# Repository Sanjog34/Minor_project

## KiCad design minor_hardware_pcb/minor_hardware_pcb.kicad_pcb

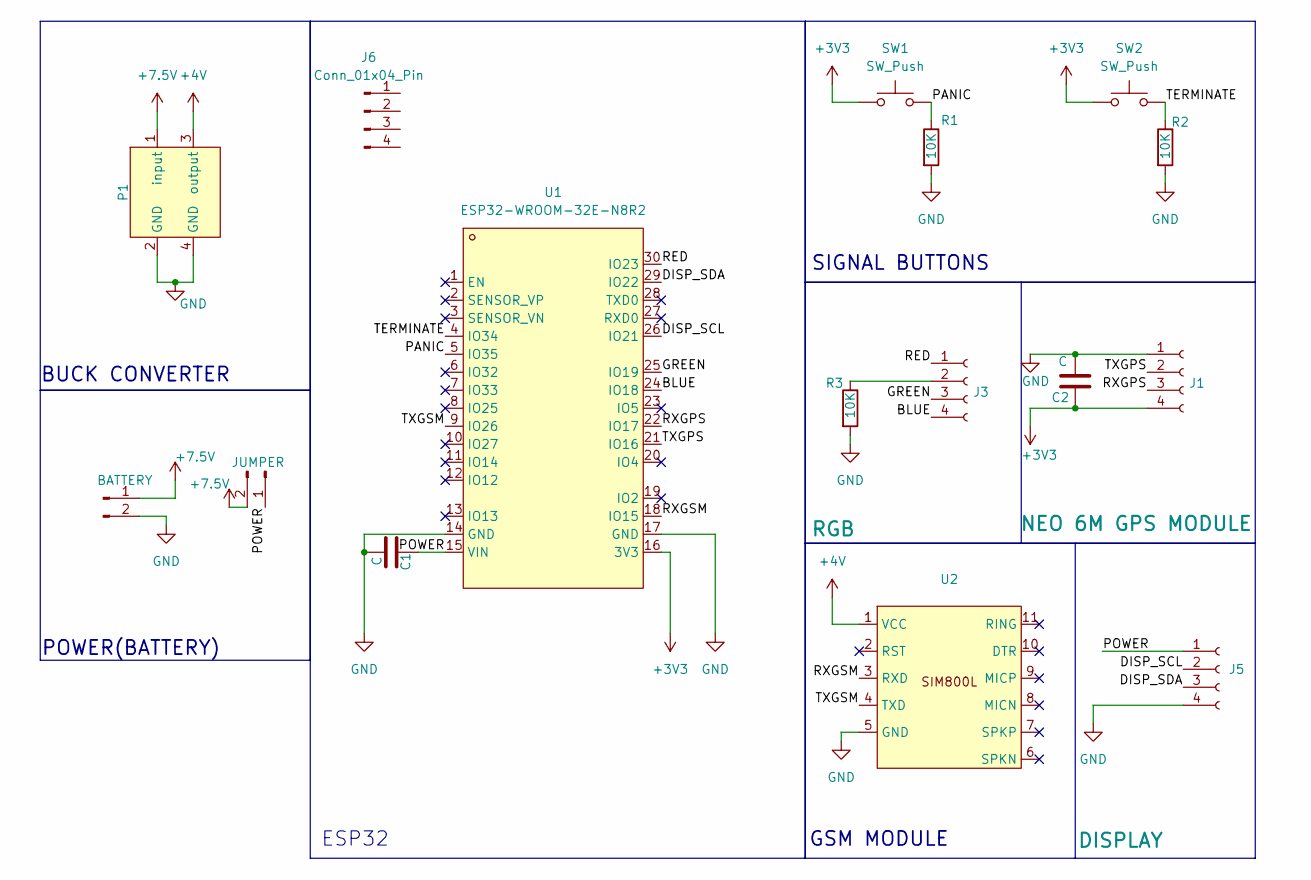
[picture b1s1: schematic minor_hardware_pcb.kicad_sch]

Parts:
C1, C2: C; CP_Radial_D8.0mm_P3.50mm
J1: NEO 6M GPS MODULE; PinSocket_1x04_P2.54mm_Vertical
J2: BATTERY; PinHeader_1x02_P2.54mm_Vertical
J3: RGB; PinSocket_1x04_P2.54mm_Vertical
J4: JUMPER; PinHeader_1x02_P2.54mm_Vertical
J5: DISPLAY; PinHeader_1x04_P2.54mm_Horizontal
J6: Conn_01x04_Pin; PinHeader_1x04_P2.54mm_Vertical
P1: dcdc_buck_lm2596_module
R1, R2, R3: 10K; R_Axial_DIN0414_L11.9mm_D4.5mm_P15.24mm_Horizontal
SW1, SW2: SW_Push; SW_PUSH_6mm
U1: ESP32-WROOM-32E-N8R2; esp32 dev board; LCSC Part C5361945
U2: sim800l

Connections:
+3V3: C2.1, J1.4, SW1.1, SW2.1, U1.16 (3V3)
+4V: P1.3 (output), U2.1 (VCC)
+7.5V: J2.1, J4.2, P1.1 (input)
/BLUE: J3.4, U1.24 (IO18)
/DISP_SCL: J5.2, U1.26 (IO21)
/DISP_SDA: J5.3, U1.29 (IO22)
/GREEN: J3.3, U1.25 (IO19)
/PANIC: R1.1, SW1.2, U1.5 (IO35)
/POWER: C1.1, J4.1, J5.1, U1.15 (VIN)
/RED: J3.1, U1.30 (IO23)
/RXGPS: J1.3, U1.22 (IO17)
/RXGSM: U1.18 (IO15), U2.3 (RXD)
/TERMINATE: R2.1, SW2.2, U1.4 (IO34)
/TXGPS: J1.2, U1.21 (IO16)
/TXGSM: U1.9 (IO26), U2.4 (TXD)
GND: C1.2, C2.2, J1.1, J2.2, J5.4, P1.2 (GND), P1.4 (GND), R1.2, R2.2, R3.2, U1.14 (GND), U1.17 (GND), U2.5 (GND)
unnamed: J3.2, R3.1

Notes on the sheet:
POWER(BATTERY)
BUCK CONVERTER
GSM MODULE
ESP32
SIGNAL BUTTONS

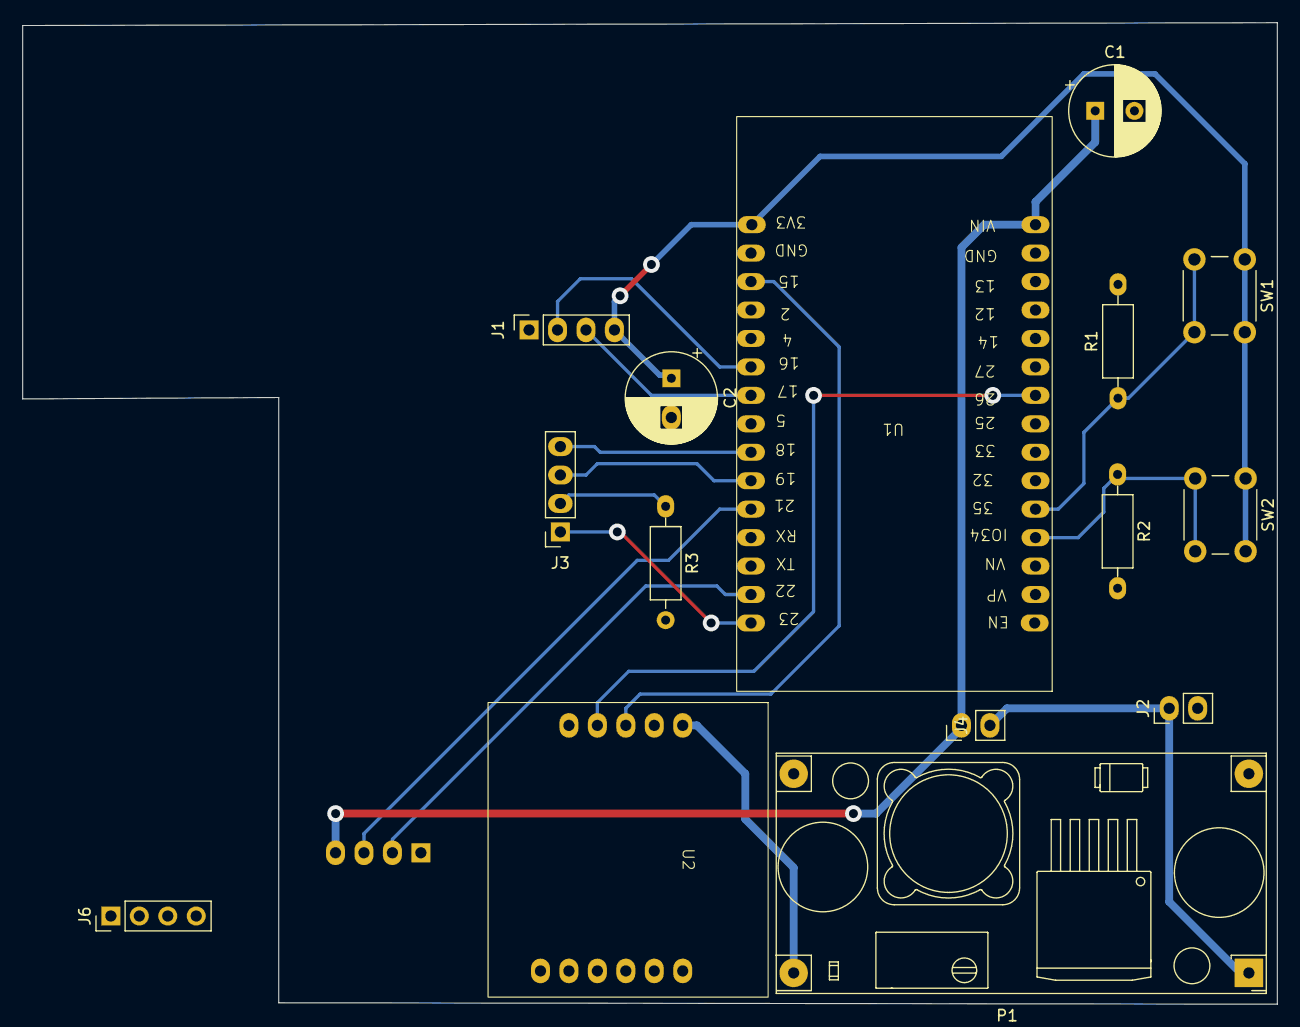
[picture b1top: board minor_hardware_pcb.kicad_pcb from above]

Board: 2 copper layers, 112.0 x 87.6 mm, 16 parts (1 on the bottom side), 17 nets.

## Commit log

2025-02-11 upload to github
2025-02-11 upload
2025-02-12 update in main code
